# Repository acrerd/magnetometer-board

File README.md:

# Magnetometer schematic and printed circuit board
Printed circuit board design for the magnetometer honours project

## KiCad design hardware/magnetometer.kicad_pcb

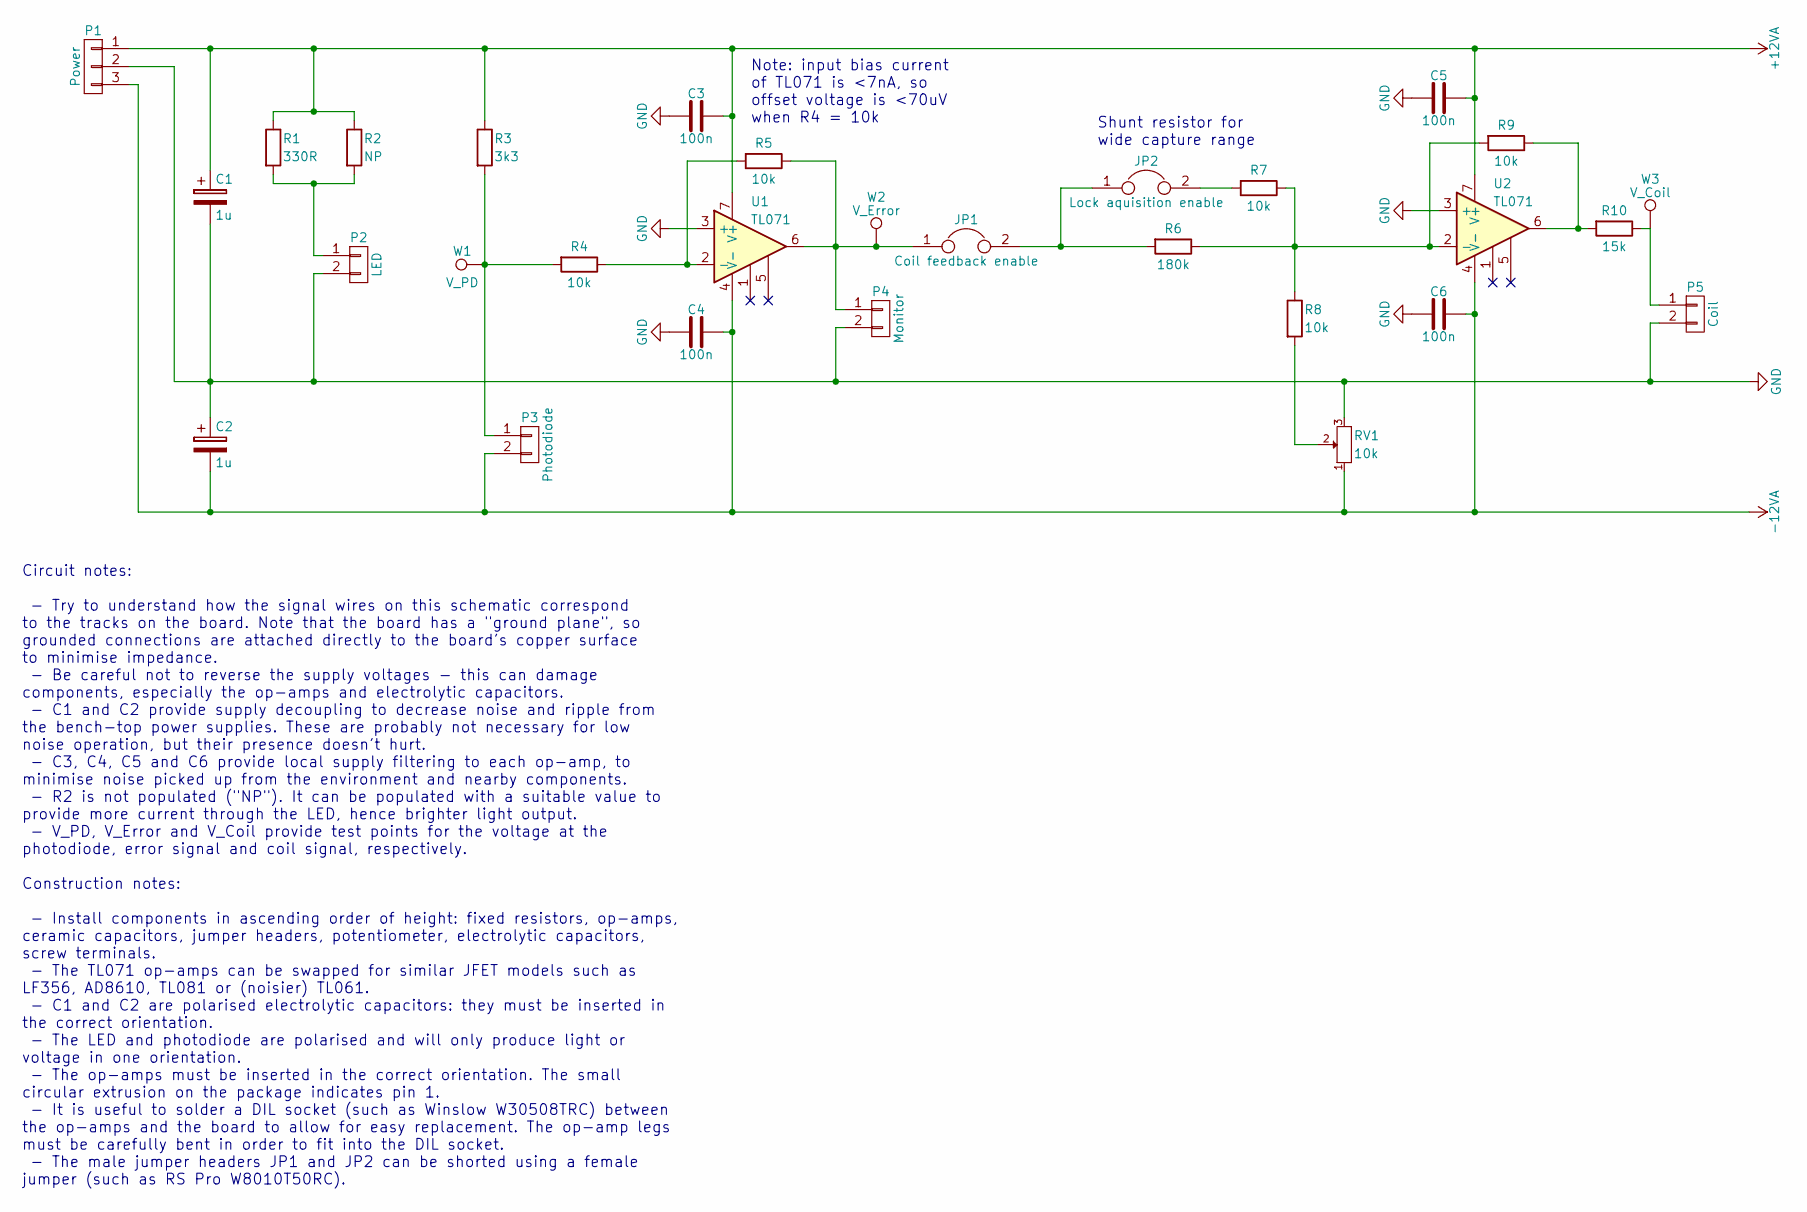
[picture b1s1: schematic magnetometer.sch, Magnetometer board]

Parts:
C1, C2: 1u; C_Radial_D5_L11_P2; MPN1 711-1407
C3, C4, C5, C6: 100n; C_Disc_D3_P2.5; MPN1 SR205E104MARTR
JP1: Coil feedback enable; Pin_Header_Straight_1x02; MPN1 W81102T3825RC
JP2: Lock aquisition enable; Pin_Header_Straight_1x02; MPN1 W81102T3825RC
P1: Power; TerminalBlock_Pheonix_MKDS1.5-3pol; MPN1 1751251
P2: LED; TerminalBlock_Pheonix_MKDS1.5-2pol; MPN1 1751248
P3: Photodiode; TerminalBlock_Pheonix_MKDS1.5-2pol; MPN1 1751248
P4: Monitor; TerminalBlock_Pheonix_MKDS1.5-2pol; MPN1 1751248
P5: Coil; TerminalBlock_Pheonix_MKDS1.5-2pol; MPN1 1751248
R1: 330R; Resistor_Horizontal_RM10mm; MPN1 707-7622
R2: NP; Resistor_Horizontal_RM10mm
R3: 3k3; Resistor_Horizontal_RM10mm; MPN1 707-7701
R4, R5, R7, R8, R9: 10k; Resistor_Horizontal_RM10mm; MPN1 707-7745
R6: 180k; Resistor_Horizontal_RM10mm; MPN1 707-7846
R10: 15k; Resistor_Horizontal_RM10mm; MPN1 707-7760
RV1: 10k; Potentiometer_Bourns_3296W_3-8Zoll_Inline_ScrewUp; MPN1 3296W-1-103LF
U1, U2: TL071; DIP-8_W7.62mm; MPN1 TL071ACP
W1: V_PD; SolderWirePad_single_1-2mmDrill
W2: V_Error; SolderWirePad_single_1-2mmDrill
W3: V_Coil; SolderWirePad_single_1-2mmDrill

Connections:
+12VA: C1.1, C3.1, C5.1, P1.1, R1.1, R2.1, R3.1, U1.7 (V+), U2.7 (V+)
-12VA: C2.2, C4.1, C6.1, P1.3, P3.2, RV1.1, U1.4 (V-), U2.4 (V-)
GND: C1.2, C2.1, C3.2, C4.2, C5.2, C6.2, P1.2, P2.2, P4.2, P5.2, RV1.3, U1.3 (+), U2.3 (+)
unnamed: JP1.1, P4.1, R5.1, U1.6, W2.1
unnamed: JP1.2, JP2.1, R6.2
unnamed: JP2.2, R7.2
unnamed: P2.1, R1.2, R2.2
unnamed: P3.1, R3.2, R4.2, W1.1
unnamed: P5.1, R10.1, W3.1
unnamed: R4.1, R5.2, U1.2 (-)
unnamed: R6.1, R7.1, R8.1, R9.2, U2.2 (-)
unnamed: R8.2, RV1.2
unnamed: R9.1, R10.2, U2.6

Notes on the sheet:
Note: input bias current of TL071 is <7nA, so offset voltage is <70uV when R4 = 10k
Shunt resistor for wide capture range
Circuit notes: - Try to understand how the signal wires on this schematic correspond to the tracks on the board. Note that the board has a "ground plane", so grounded connections are attached directly to the board's copper surface to minimise impedance. - Be careful not to reverse the supply voltag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

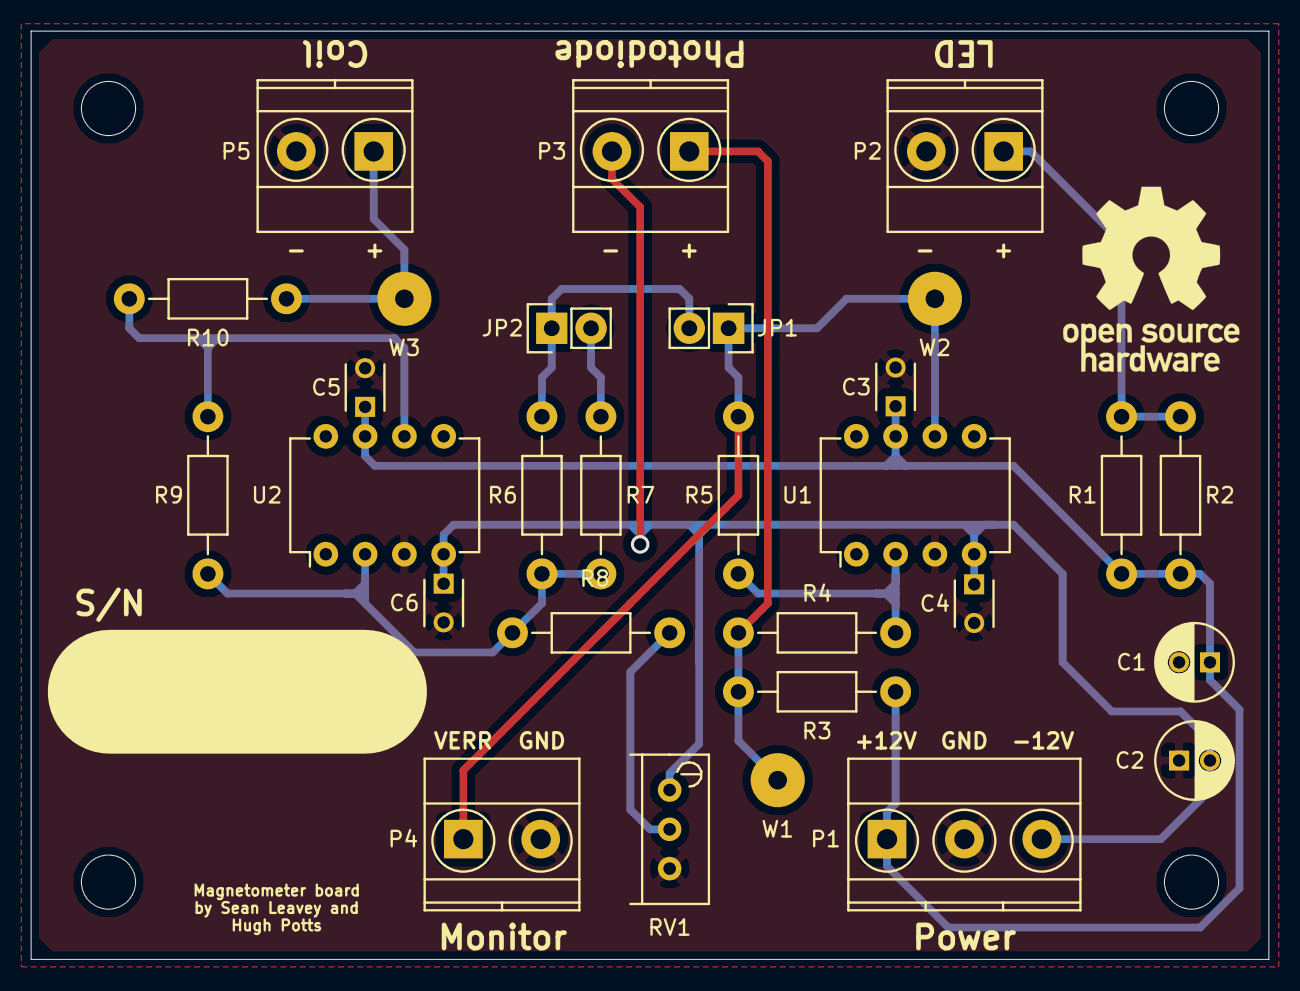
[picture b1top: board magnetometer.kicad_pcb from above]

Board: 2 copper layers, 80.0 x 60.0 mm, 30 parts (0 on the bottom side), 13 nets.

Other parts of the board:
Ref**: Val**; 80mmx60mm_holes

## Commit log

2017-10-13 Draft schematic
2017-10-13 Modify readme
2017-10-21 Board design
2017-10-23 Gerber files for version 1
2017-10-23 Update page properties
2017-10-23 Bill of materials
2017-10-23 Board pictures for assembly
